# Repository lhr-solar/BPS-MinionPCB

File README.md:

# BPS Voltage Temperature Minion PCB

## Purpose
This board communicates with the [Leader Board](https://github.com/lhr-solar/BPS-LeaderPCB) over ISOSPI. It is capable of reading up to 12 voltage measurements and 16 temperature measurements. It is also capable of implementing battery balancing through the LTC6811.

## Connectors
* Two 10 pin headers that are used to place the [Minion Hat Board](https://github.com/lhr-solar/BPS-MinionShieldPCB) on top
* Two 7 pin connectors that are used to connect the voltage taps to the board
* Two 2 pin connectors for ISOSPI communication

## BOM
[Mouser cart](https://www.mouser.com/ProjectManager/ProjectDetail.aspx?AccessID=1d4073bff4) of all the components that cannot be sampled.

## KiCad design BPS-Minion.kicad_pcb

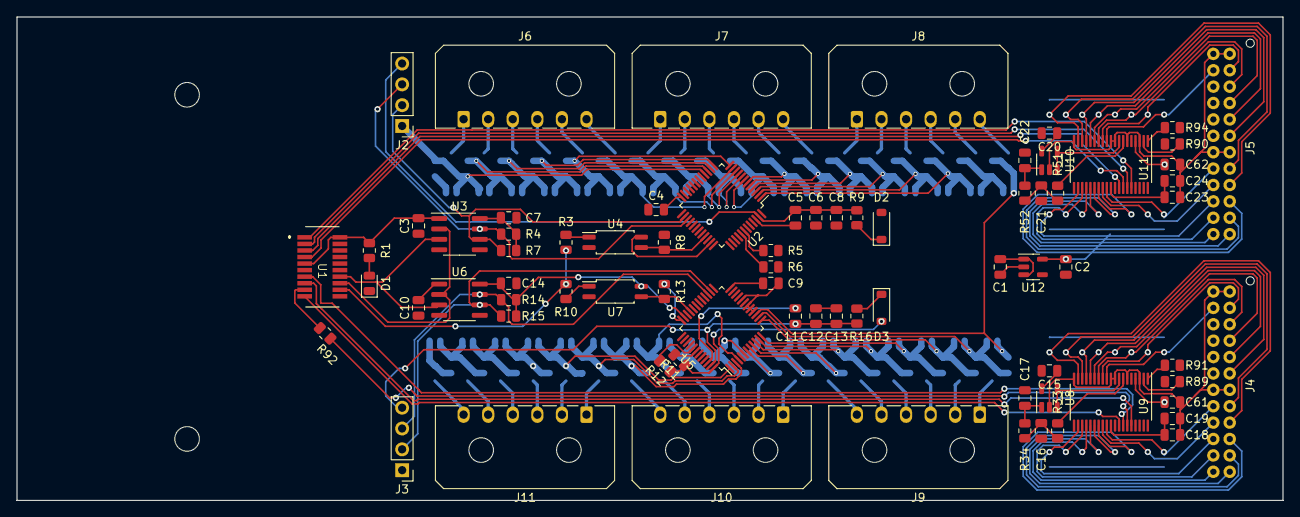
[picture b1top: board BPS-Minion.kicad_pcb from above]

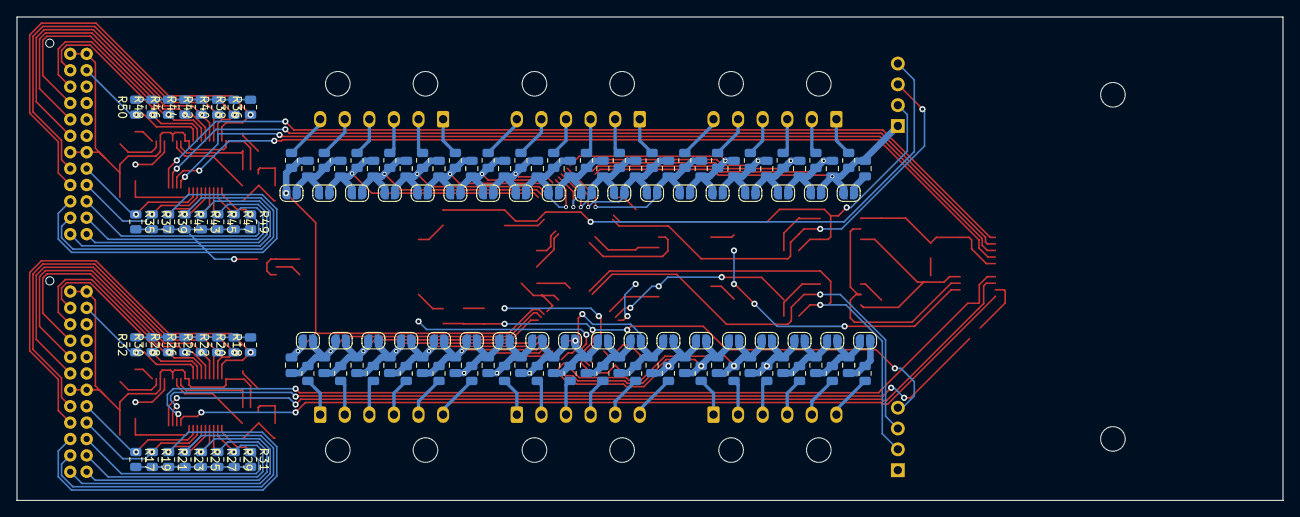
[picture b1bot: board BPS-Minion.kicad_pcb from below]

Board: 2 copper layers, 154.5 x 59.0 mm, 219 parts (140 on the bottom side), 156 nets.

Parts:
C1, C61, C62: 10uF; C_0805_2012Metric
C2, C3, C7, C8, C10, C13, C14, C15, C18, C19, C20, C23, C24: 1uF; C_0805_2012Metric
C4, C9: 4.7uF; C_0805_2012Metric
C5, C11: 0.47uF; C_0805_2012Metric
C6, C12: 100pF; C_0805_2012Metric
C16, C17, C21, C22: 47nF; C_0805_2012Metric
C25, C26, C27, C28, C29, C30, C31, C32, C33, C34, C35, C36, C37, C38, C39, C40, C41, C42, C43, C44, C45, C46, C47, C48, C49, C50, C51, C52, C53, C54, C55, C56, C57, C58, C59, C60: 220nF; C_0805_2012Metric
D1: Green; LED_0805_2012Metric
D2, D3: 1N4448W; D_SOD-123
J2: BMS1OTP; PinHeader_1x04_P2.54mm_Vertical
J3: BMS2OTP; PinHeader_1x04_P2.54mm_Vertical
J4, J5: Conn_01x24_Female; B24B-PADSS-F
J6, J7, J8, J9, J10, J11: TopConn; Molex_Micro-Fit_3.0_43650-0600_1x06_P3.00mm_Horizontal
MH1, MH2, MH3, MH4: M3; MountingHole_3mm
R1, R13: 1k; R_0805_2012Metric
R3, R10: 220; R_0805_2012Metric
R4, R5, R6, R7, R8, R11, R12, R14, R15, R17, R18, R19, R20, R21, R22, R23, R24, R25, R26, R27, R28, R29, R30, R31, R32, R35, R36, R37, R38, R39, R40, R41, R42, R43, R44, R45, R46, R47, R48, R49, R50: 10k; R_0805_2012Metric
R9, R16: 100; R_0805_2012Metric
R33, R34, R51, R52: 4.7k; R_0805_2012Metric
R53, R54, R55, R56, R57, R58, R59, R60, R61, R62, R63, R64, R65, R66, R67, R68, R69, R70, R71, R72, R73, R74, R75, R76, R77, R78, R79, R80, R81, R82, R83, R84, R85, R86, R87, R88: 20; R_0805_2012Metric
R89, R90, R91, R94: 100k; R_0805_2012Metric
R92: 50; R_0805_2012Metric
TP1, TP2, TP3, TP4, TP5, TP6, TP7, TP8, TP9, TP10, TP11, TP12, TP13, TP14, TP15, TP16, TP17, TP18, TP19, TP20, TP21, TP22, TP23, TP24, TP25, TP26, TP27, TP28, TP29, TP30, TP31, TP32, TP33, TP34, TP35, TP36: TestPoint_2Pole; SolderJumper-2_P1.3mm_Open_RoundedPad1.0x1.5mm
U1: PeripheralSOM
U2, U5: BQ7695201PFBR; TQFP-48_7x7mm_P0.5mm
U3, U6: ISO1640BDR; SOIC-8_3.9x4.9mm_P1.27mm
U4, U7: EL3H7; SOP-4_4.4x2.6mm_P1.27mm
U8, U10: LM321; SOT-23-5
U9, U11: ADS7953SBDBT; TSSOP-38_4.4x9.7mm_P0.5mm
U12: MIC5317-2.5xM5; SOT-23-5

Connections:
+2V5: C2.1, C61.2, C62.2, R17.2, R18.2, R19.2, R20.2, R21.2, R22.2, R23.2, R24.2, R25.2, R26.2, R27.2, R28.2, R29.2, R30.2, R31.2, R32.2, R35.2, R36.2, R37.2, R38.2, R39.2, R40.2, R41.2, R42.2, R43.2, R44.2, R45.2, R46.2, R47.2, R48.2, R49.2, R50.2, U9.4 (REFP), U11.4 (REFP), U12.5 (VOUT)
+3.3V: C3.2, C10.2, C15.2, C20.2, R1.2, R89.1, R90.1, U1.2 (+3.3V), U1.9 (+3.3V), U3.1 (VCC1), U6.1 (VCC1), U8.5 (V+), U9.36 (VBD+), U10.5 (V+), U11.36 (VBD+)
/BMS/BMS1BAT: C5.2, C6.2, C8.2, J2.4, R9.1, U2.47 (BAT)
/BMS/BMS1Reg1: C7.1, R4.1, R7.1, U2.35 (REG1), U3.8 (VCC2), U4.4
/BMS/BMS1Reset: R8.2, U2.33 (RST_SHUT), U4.3
/BMS/BMS1SCL: J2.2, R7.2, U2.26 (SCL), U3.6 (SCL2)
/BMS/BMS1SDA: J2.3, R4.2, U2.27 (SDA), U3.7 (SDA2)
/BMS/BMS2BAT: C11.2, C12.2, C13.2, J3.4, R16.1, U5.47 (BAT)
/BMS/BMS2Reg1: C14.1, R14.1, R15.1, U5.35 (REG1), U6.8 (VCC2), U7.4
/BMS/BMS2Reset: R13.2, U5.33 (RST_SHUT), U7.3
/BMS/BMS2SCL: J3.2, R15.2, U5.26 (SCL), U6.6 (SCL2)
/BMS/BMS2SDA: J3.3, R14.2, U5.27 (SDA), U6.7 (SDA2)
/BMS/BatteryConnector6/cell4+: C58.1, C59.2, R86.2, TP34.2, TP35.1
/BMS/BatteryConnector6/cell5+: C59.1, C60.2, R87.2, TP35.2, TP36.1
/BMS/BatteryConnector6/cell6+: C60.1, R88.2, TP36.2
/BMS/cell1: C26.1, C27.2, R54.2, TP2.2, TP3.1, U2.15 (VC1)
/BMS/cell2: C27.1, C28.2, R55.2, TP3.2, TP4.1, U2.14 (VC2)
/BMS/cell3: C28.1, C29.2, R56.2, TP4.2, TP5.1, U2.13 (VC3)
/BMS/cell4: C29.1, C30.2, R57.2, TP5.2, TP6.1, U2.12 (VC4)
/BMS/cell5: C30.1, C31.2, R58.2, TP6.2, TP7.1, U2.11 (VC5)
/BMS/cell6: C31.1, C32.2, R59.2, TP7.2, TP8.1, U2.10 (VC6)
/BMS/cell7: C32.1, C33.2, R60.2, TP8.2, TP9.1, U2.9 (VC7)
/BMS/cell8: C33.1, C34.2, R61.2, TP9.2, TP10.1, U2.8 (VC8)
/BMS/cell9: C34.1, C35.2, R62.2, TP10.2, TP11.1, U2.7 (VC9)
/BMS/cell10: C35.1, C36.2, R63.2, TP11.2, TP12.1, U2.6 (VC10)
/BMS/cell11: C36.1, C37.2, R64.2, TP12.2, TP13.1, U2.5 (VC11)
/BMS/cell12: C37.1, C38.2, R65.2, TP13.2, TP14.1, U2.4 (VC12)
/BMS/cell13: C38.1, C39.2, R66.2, TP14.2, TP15.1, U2.3 (VC13)
/BMS/cell14: C39.1, C40.2, R67.2, TP15.2, TP16.1, U2.2 (VC14)
/BMS/cell15: C40.1, C41.2, R68.2, TP16.2, TP17.1, U2.1 (VC15)
/BMS/cell17: C42.1, C43.2, R70.2, TP18.2, TP19.1, U5.15 (VC1)
/BMS/cell18: C43.1, C44.2, R71.2, TP19.2, TP20.1, U5.14 (VC2)
/BMS/cell19: C44.1, C45.2, R72.2, TP20.2, TP21.1, U5.13 (VC3)
/BMS/cell20: C45.1, C46.2, R73.2, TP21.2, TP22.1, U5.12 (VC4)
/BMS/cell21: C46.1, C47.2, R74.2, TP22.2, TP23.1, U5.11 (VC5)
/BMS/cell22: C47.1, C48.2, R75.2, TP23.2, TP24.1, U5.10 (VC6)
/BMS/cell23: C48.1, C49.2, R76.2, TP24.2, TP25.1, U5.9 (VC7)
/BMS/cell24: C49.1, C50.2, R77.2, TP25.2, TP26.1, U5.8 (VC8)
/BMS/cell25: C50.1, C51.2, R78.2, TP26.2, TP27.1, U5.7 (VC9)
/BMS/cell26: C51.1, C52.2, R79.2, TP27.2, TP28.1, U5.6 (VC10)
/BMS/cell27: C52.1, C53.2, R80.2, TP28.2, TP29.1, U5.5 (VC11)
/BMS/cell28: C53.1, C54.2, R81.2, TP29.2, TP30.1, U5.4 (VC12)
/BMS/cell29: C54.1, C55.2, R82.2, TP30.2, TP31.1, U5.3 (VC13)
/BMS/cell30: C55.1, C56.2, R83.2, TP31.2, TP32.1, U5.2 (VC14)
/BMS/cell31: C56.1, C57.2, R84.2, TP32.2, TP33.1, U5.1 (VC15)
/BMS/cell32: C57.1, C58.2, D3.2 (A), R11.1, R12.1, R85.2, TP33.2, TP34.1, U5.48 (VC16)
/I2C1_SCL: U1.14 (I2C1_SCL), U3.3 (SCL1), U6.3 (SCL1)
/I2C1_SDA: U1.16 (I2C1_SDA), U3.2 (SDA1), U6.2 (SDA1)
/PA2: R3.1, R10.1, U1.18 (PA2(ADC))
/SPI1_MISO: U1.15 (SPI1_MISO), U9.34 (SDO)
/SPI1_MOSI: R92.1, U9.33 (SDI)
/SPI1_NSS: U1.19 (SPI1_NSS), U9.31 (*CS)
/SPI1_SCK: U1.13 (SPI1_SCK), U9.32 (SCLK)
/SPI2_MISO: U1.3 (SPI2_MISO), U11.33 (SDI)
/SPI2_MOSI: U1.1 (SPI2_MOSI), U11.34 (SDO)
/SPI2_NSS: U1.7 (SPI2_NSS), U11.32 (SCLK)
/SPI2_SCK: U1.5 (SPI2_SCK), U11.31 (*CS)
/Temperature1/ADCIN: U10.3 (-), U10.4, U11.8 (AINP)
/Temperature1/MUXOUT: R51.2, U11.7 (MXO)
/Temperature1/temp1: J5.16, R35.1, U11.28 (CH0)
/Temperature1/temp2: J5.18, R37.1, U11.27 (CH1)
/Temperature1/temp3: J5.19, R39.1, U11.26 (CH2)
/Temperature1/temp4: J5.21, R41.1, U11.25 (CH3)
/Temperature1/temp5: J5.23, R43.1, U11.24 (CH4)
/Temperature1/temp6: J5.24, R45.1, U11.23 (CH5)
/Temperature1/temp7: J5.22, R47.1, U11.22 (CH6)
/Temperature1/temp8: J5.20, R49.1, U11.21 (CH7)
/Temperature1/temp9: J5.17, R36.1, U11.18 (CH8)
/Temperature1/temp10: J5.15, R38.1, U11.17 (CH9)
/Temperature1/temp11: J5.11, R40.1, U11.16 (CH10)
/Temperature1/temp12: J5.9, R42.1, U11.15 (CH11)
/Temperature1/temp13: J5.7, R44.1, U11.14 (CH12)
/Temperature1/temp14: J5.5, R46.1, U11.13 (CH13)
/Temperature1/temp15: J5.3, R48.1, U11.12 (CH14)
/Temperature1/temp16: J5.4, R50.1, U11.11 (CH15)
/Temperature/ADCIN: U8.3 (-), U8.4, U9.8 (AINP)
/Temperature/MUXOUT: R33.2, U9.7 (MXO)
/Temperature/temp1: J4.16, R17.1, U9.28 (CH0)
/Temperature/temp2: J4.18, R19.1, U9.27 (CH1)
/Temperature/temp3: J4.19, R21.1, U9.26 (CH2)
/Temperature/temp4: J4.21, R23.1, U9.25 (CH3)
/Temperature/temp5: J4.23, R25.1, U9.24 (CH4)
/Temperature/temp6: J4.24, R27.1, U9.23 (CH5)
/Temperature/temp7: J4.22, R29.1, U9.22 (CH6)
/Temperature/temp8: J4.20, R31.1, U9.21 (CH7)
/Temperature/temp9: J4.17, R18.1, U9.18 (CH8)
/Temperature/temp10: J4.15, R20.1, U9.17 (CH9)
/Temperature/temp11: J4.11, R22.1, U9.16 (CH10)
/Temperature/temp12: J4.9, R24.1, U9.15 (CH11)
/Temperature/temp13: J4.7, R26.1, U9.14 (CH12)
/Temperature/temp14: J4.5, R28.1, U9.13 (CH13)
/Temperature/temp15: J4.3, R30.1, U9.12 (CH14)
/Temperature/temp16: J4.4, R32.1, U9.11 (CH15)
GND: C3.1, C10.1, C15.1, C20.1, D1.1 (K), R91.2, R94.2, U1.4 (GND), U1.11 (GND), U3.4 (GND1), U4.2, U6.4 (GND1), U7.2, U9.35 (BDGND), U11.35 (BDGND)
GND1: C4.1, C6.1, C7.2, C8.1, C25.1, C25.2, C26.2, J2.1, R8.1, R53.2, TP1.1, TP1.2, TP2.1, U2.16 (VC0), U2.17 (VSS), U2.18 (SRP), U2.20 (SRN), U2.36 (REGIN), U2.37 (BREG), U3.5 (GND2)
GND2: C9.1, C12.1, C13.1, C14.2, C41.1, C42.2, D2.2 (A), J3.1, R5.1, R6.1, R13.1, R69.2, TP17.2, TP18.1, U2.48 (VC16), U5.16 (VC0), U5.17 (VSS), U5.18 (SRP), U5.20 (SRN), U5.36 (REGIN), U5.37 (BREG), U6.5 (GND2)
GNDA: C1.1, C2.2, C16.1, C17.1, C18.2, C19.2, C21.1, C22.1, C23.2, C24.2, C61.1, C62.1, J4.1, J4.2, J4.13, J4.14, J5.1, J5.2, J5.13, J5.14, U1.12 (GNDA), U8.2 (V-), U9.3 (REFM), U9.6 (AGND), U9.9 (AINM), U9.10 (AGND), U9.19 (AGND), U9.20 (AGND), U9.30 (AGND), U10.2 (V-), U11.3 (REFM), U11.6 (AGND), U11.9 (AINM), U11.10 (AGND), U11.19 (AGND), U11.20 (AGND), U11.30 (AGND), U12.2 (GND)
unnamed: C16.2, R33.1, R34.2
unnamed: C21.2, R51.1, R52.2
unnamed: D1.2 (A), R1.1
unnamed: D2.1 (K), R9.2
unnamed: D3.1 (K), R16.2
unnamed: J6.1, R53.1
unnamed: J6.2, R54.1
unnamed: J6.3, R55.1
unnamed: J6.4, R56.1
unnamed: J6.5, R57.1
unnamed: J6.6, R58.1
unnamed: J7.1, R59.1
unnamed: J7.2, R60.1
unnamed: J7.3, R61.1
unnamed: J7.4, R62.1
unnamed: J7.5, R63.1
unnamed: J7.6, R64.1
unnamed: J8.1, R65.1
unnamed: J8.2, R66.1
unnamed: J8.3, R67.1
unnamed: J8.4, R68.1
unnamed: J8.5, R69.1
unnamed: J8.6, R70.1
unnamed: J9.1, R71.1
unnamed: J9.2, R72.1
unnamed: J9.3, R73.1
unnamed: J9.4, R74.1
unnamed: J9.5, R75.1
unnamed: J9.6, R76.1
unnamed: J10.1, R77.1
unnamed: J10.2, R78.1
unnamed: J10.3, R79.1
unnamed: J10.4, R80.1
unnamed: J10.5, R81.1
unnamed: J10.6, R82.1
unnamed: J11.1, R83.1
unnamed: J11.2, R84.1
unnamed: J11.3, R85.1
unnamed: J11.4, R86.1
unnamed: J11.5, R87.1
unnamed: J11.6, R88.1
unnamed: R3.2, U4.1
unnamed: R10.2, U7.1
unnamed: R92.2, U1.17 (SPI1_MOSI)
unnamed: C5.1, U2.46 (CP1)
unnamed: R6.2, U2.41 (LD)
unnamed: R5.2, U2.42 (PACK)
unnamed: C4.2, U2.24 (REG18)
unnamed: C11.1, U5.46 (CP1)
unnamed: R12.2, U5.41 (LD)
unnamed: R11.2, U5.42 (PACK)
unnamed: C9.2, U5.24 (REG18)
unnamed: C17.2, R34.1, U8.1 (+)
unnamed: R91.1, U9.1 (GPIO2)
unnamed: R89.2, U9.2 (GPIO3)
unnamed: C22.2, R52.1, U10.1 (+)
unnamed: R94.1, U11.1 (GPIO2)
unnamed: R90.2, U11.2 (GPIO3)
VDDA: C1.2, C18.1, C19.1, C23.1, C24.1, U1.10 (VDDA(3.3V)), U9.5 (VA+), U9.29 (VA+), U11.5 (VA+), U11.29 (VA+), U12.1 (VIN), U12.3 (EN)

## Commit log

2020-08-02 Set up for own repository
2020-08-02 Makes sure everything is still good
2020-08-02 Updates gitignore
2020-08-07 Adds mouser cart link to README
2020-08-13 Updates kicad project name to match repo name
2020-09-01 Renames project to not include PCB
2020-09-19 Updates HX1188 to point to common library
2020-10-03 Adds QuAC
2020-10-10 Add STEP files. Some connectors still not shown.
2020-10-17 Adds dimensions and pdf of PCB
2022-11-12 Added measurements
2023-05-07 Removed backups, converted to KiCAD 7.0, Added Documentation & version history
2023-06-11 (Hopefully) finished standardization
2023-06-11 Moved connector directory
2023-06-11 Added 3.3V regulator
2023-06-12 Added L431CBT chip + peripherals
2023-06-12 Added can circuit
2023-06-12 Added more questions
2023-09-30 added MUX
2023-09-30 ADC implementation for scanning through thermistors
2023-09-30 schematic file for previous commit
2023-09-30 gitignore update
2023-09-30 new adc symbol
2023-10-07 ADC Power all 3.3V
2023-10-07 bms chip started
2023-10-14 BMS chip is fully wired
2023-10-14 clean up
2023-10-14 update submodule
2023-10-14 edited some mistakes out
2023-10-28 new sheets
2023-10-28 main sheet fixes
2023-10-31 temperature fixes
2023-10-31 kill backups
2023-11-04 stacked bms schematic
2023-11-04 edits to the voltage monitoring board
2023-11-04 mismatched ground
2023-11-04 final edits
2023-11-04 power flags
2023-11-04 power fixes
2023-12-02 bypass capacitors
2023-12-02 lakshay changes:
2023-12-02 started pcb
2023-12-16 define edge cuts for new volttemp
2023-12-18 battery pack draft design
2023-12-18 battery pack half done
2023-12-21 why so many bugs >:(
2023-12-26 Fixed minor bugs with BMS and temp chips
2023-12-27 Forgot to add footprints and values + updated PCB froms schematic
2023-12-27 Use PeripheralSOM symbol
2024-01-03 submodule fixes and updte PCB
2024-01-08 started layout
2024-01-09 minor temp changes
2024-01-09 new temp layout (bottom one)
2024-01-09 time flies when you're kicadding :(
2024-01-09 wheeeeeee
2024-01-10 killed all the COMMONers
2024-01-14 new ADC layout
2024-01-20 update solder mask
2024-01-30 literal piss and shit
2024-01-31 footprint changes
2024-01-31 drcs
2024-02-03 fix gnd2
2024-02-03 moved and grouped components, need to change temp connector adc and passives
2024-02-10 placed all the components :smile:
2024-02-10 TI GNDing is weirddd
2024-02-10 layed out adc components, abt 75% done probably?
2024-02-17 Revert "layed out adc components, abt 75% done probably?"
    This reverts commit 5305dcecdd1d1d4d875daf20a76a2afe21639337.
2024-02-17 start wiring
2024-03-02 more wiring
2024-03-02 finished wiring except for gnd+pwr planing
2024-03-08 fixed submodule cuz it was annoying me
